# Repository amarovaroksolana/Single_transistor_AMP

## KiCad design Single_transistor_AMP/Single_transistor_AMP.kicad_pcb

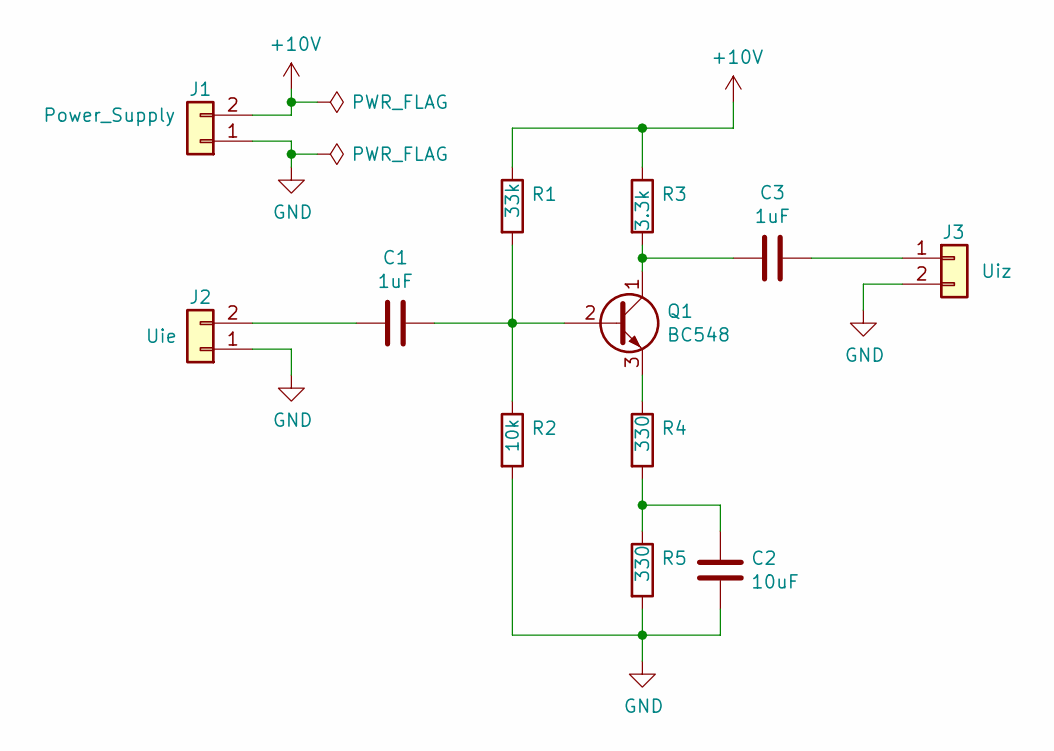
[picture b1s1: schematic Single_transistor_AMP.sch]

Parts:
C1, C3: 1uF; C_Rect_L4.0mm_W2.5mm_P2.50mm
C2: 10uF; C_Rect_L4.0mm_W2.5mm_P2.50mm
J1: Power_Supply; PinHeader_1x02_P2.54mm_Vertical
J2: Uie; PinHeader_1x02_P2.54mm_Vertical
J3: Uiz; PinHeader_1x02_P2.54mm_Vertical
Q1: BC548; TO-92_Inline
R1: 33k; R_Axial_DIN0207_L6.3mm_D2.5mm_P10.16mm_Horizontal
R2: 10k; R_Axial_DIN0207_L6.3mm_D2.5mm_P10.16mm_Horizontal
R3: 3.3k; R_Axial_DIN0207_L6.3mm_D2.5mm_P10.16mm_Horizontal
R4, R5: 330; R_Axial_DIN0207_L6.3mm_D2.5mm_P10.16mm_Horizontal

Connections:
+10V: J1.2, R1.1, R3.1
GND: C2.2, J1.1, J2.1, J3.2, R2.2, R5.2
unnamed: C1.1, Q1.2 (B), R1.2, R2.1
unnamed: C1.2, J2.2
unnamed: C2.1, R4.2, R5.1
unnamed: C3.1, J3.1
unnamed: C3.2, Q1.1 (C), R3.2
unnamed: Q1.3 (E), R4.1

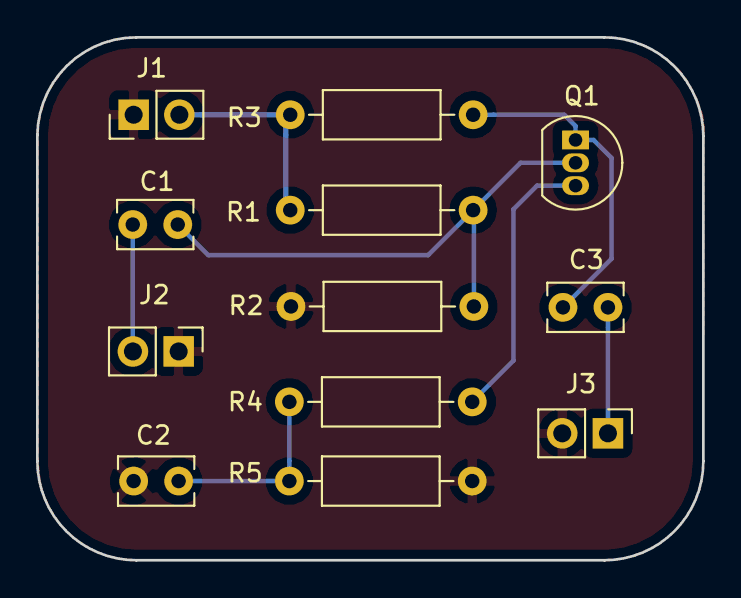
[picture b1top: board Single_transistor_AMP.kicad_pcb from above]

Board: 2 copper layers, 37.0 x 29.0 mm, 12 parts (0 on the bottom side), 8 nets.

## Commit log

2019-03-20 Majas darbs Nr.4
2019-03-30 Majas darbs Nr.6
2019-04-07 Majas darbs Nr.7
2019-04-08 Majas darbs Nr.8
2019-04-22 Majas darbs Nr.9
2019-05-02 Majas darbs 10
